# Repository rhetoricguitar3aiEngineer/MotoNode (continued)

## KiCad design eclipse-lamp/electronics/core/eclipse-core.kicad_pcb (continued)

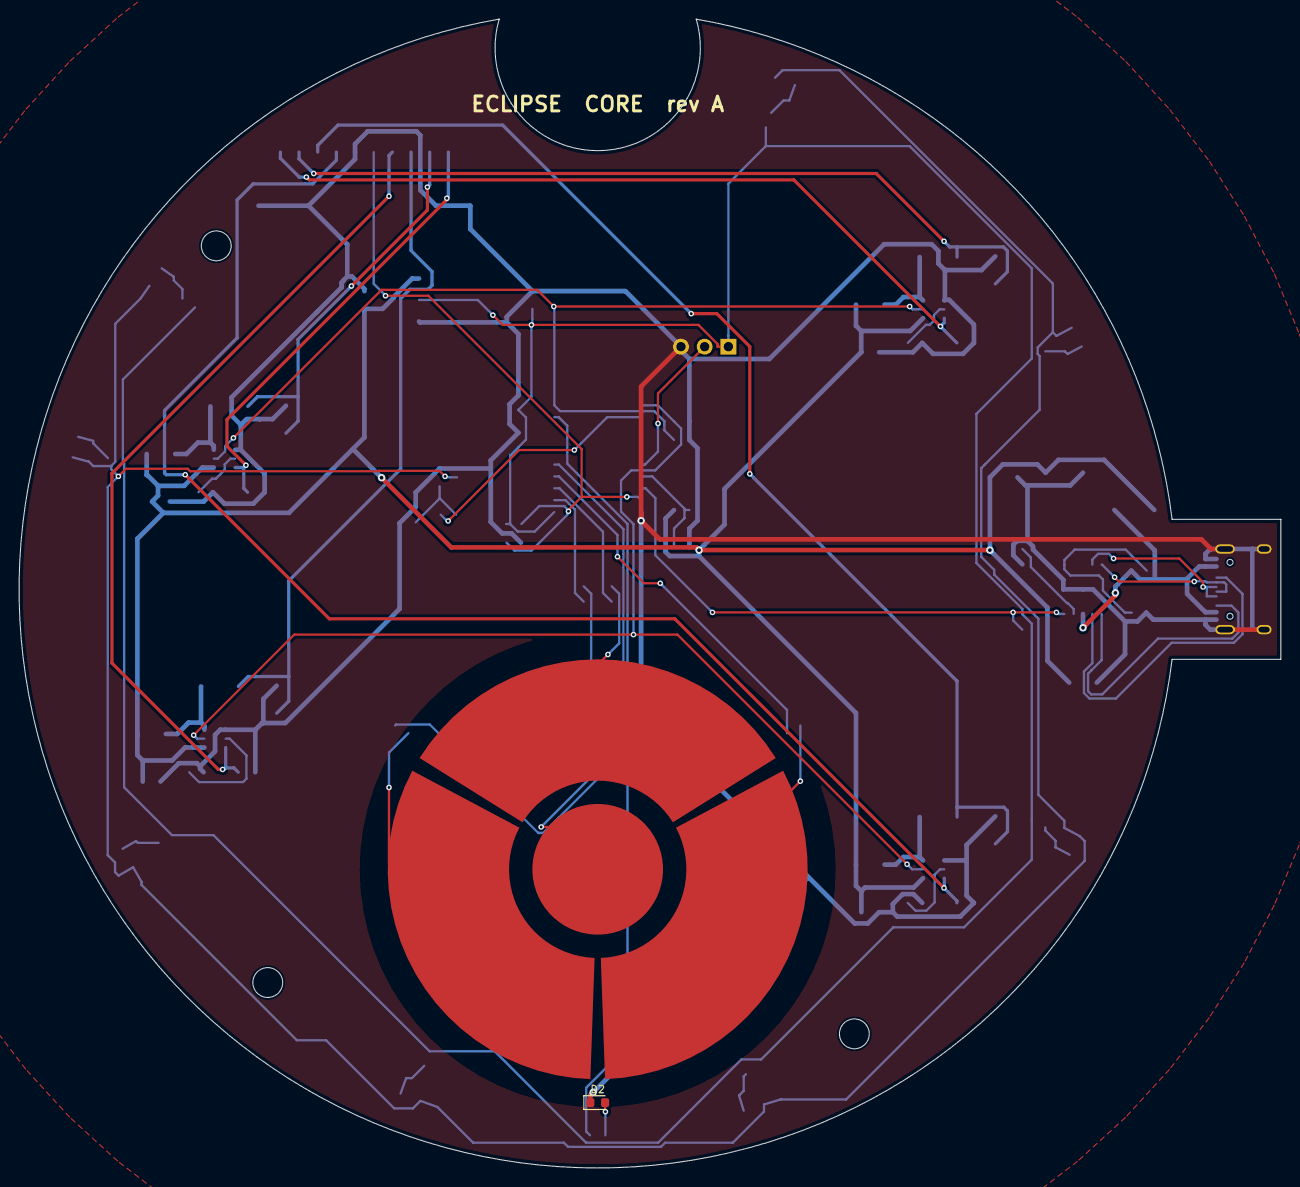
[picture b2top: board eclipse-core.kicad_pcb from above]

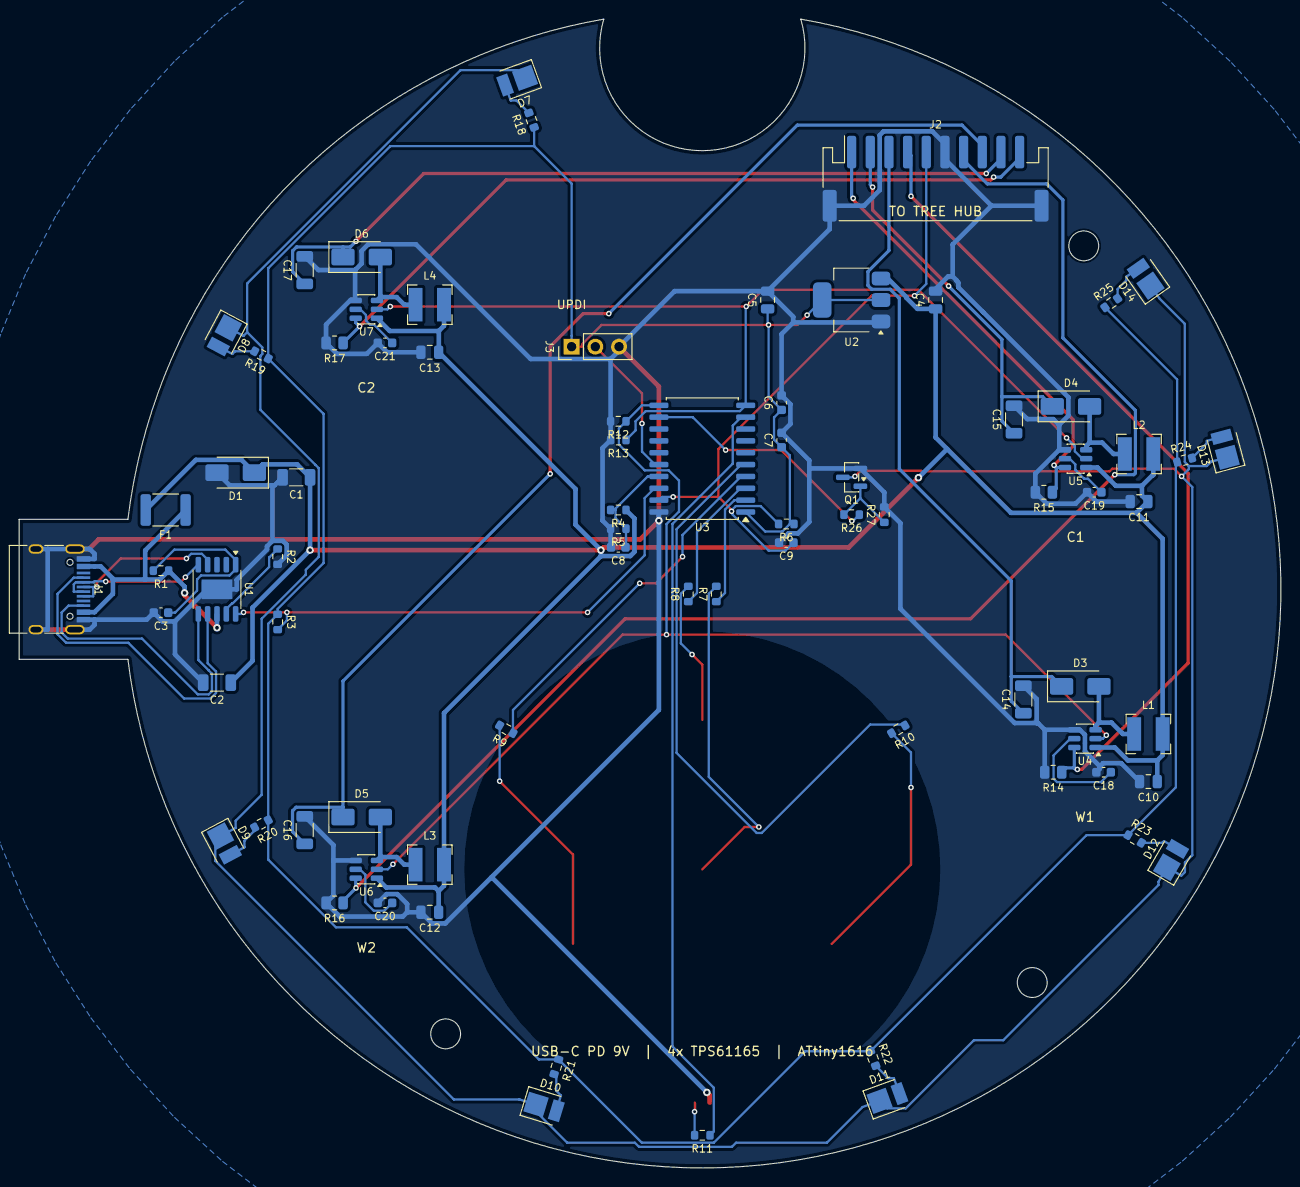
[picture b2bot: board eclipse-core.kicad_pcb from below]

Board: 2 copper layers, 135.2 x 123.1 mm, 85 parts (80 on the bottom side), 53 nets.

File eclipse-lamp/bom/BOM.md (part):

# ECLIPSE Tree - Bill of Materials

Generated by `make_bom.py` from the KiCad schematics plus the mechanical parts list.
Unit prices are **budgetary estimates** (USD, 1k-unit volume). Re-quote before ordering.

## Core board (base)

| Refs | Qty | Value | Description | Manufacturer | MPN | Unit $ | Ext $ |
|---|---:|---|---|---|---|---:|---:|
| C1,C2 | 2 | 22uF 25V | Input bulk | Murata | GRM31CR61E226KE15L | 0.060 | 0.12 |
| C3,C7 | 2 | 1uF | CH224K VDD decoupling,MCU decoupling | Murata | GRM188R61E105KA12D | 0.006 | 0.01 |
| C4 | 1 | 10uF | LDO input | Samsung | CL21A106KAYNNNE | 0.020 | 0.02 |
| C5 | 1 | 22uF | LDO output | Samsung | CL21A226MAQNNNE | 0.020 | 0.02 |
| C6,C8,C9 | 3 | 100nF | MCU decoupling | Murata | GRM188R71H104KA93D | 0.004 | 0.01 |
| C10,C11,C12,C13 | 4 | 10uF 25V | Boost input | Samsung | CL21A106KAYNNNE | 0.020 | 0.08 |
| C14,C15,C16,C17 | 4 | 1uF 50V | Boost output | Murata | GRM31MR71H105KA88L | 0.040 | 0.16 |
| C18,C19,C20,C21 | 4 | 220nF | Loop compensation | Murata | GRM188R71E224KA88D | 0.006 | 0.02 |
| D1 | 1 | SMAJ15CA | TVS 15 V standoff, bidirectional, 400 W | Littelfuse | SMAJ15CA | 0.050 | 0.05 |
| D2 | 1 | WHITE | 0603 white - glow under touch glass | Lite-On | LTW-C191TS5 | 0.030 | 0.03 |
| D3,D4,D5,D6 | 4 | MBRA160 | Schottky 60 V 1 A | onsemi | MBRA160T3G | 0.060 | 0.24 |
| D7,D8,D9,D10,D11,D12,D13,D14 | 8 | 2700K | 2835 warm white, fires down into the white-lined base cavity | Samsung | LM281B+ 2700K | 0.030 | 0.24 |
| F1 | 1 | 1.5A | PTC resettable fuse 1.5 A hold, 24 V | Bourns | MF-MSMF150/24X-2 | 0.100 | 0.10 |
| J1 | 1 | USB-C 16P | USB Type-C receptacle, 16P, SMD + THT shell | Korean Hroparts | TYPE-C-31-M-12 | 0.120 | 0.12 |
| J2 | 1 | TO HUB | PH 2.0 mm 10-pin side-entry SMD | JST | S10B-PH-SM4-TB | 0.250 | 0.25 |
| J3 | 1 | UPDI | UPDI programming header (DNP) | - | DNP (pogo pads) | 0.000 | 0.00 |
| L1,L2,L3,L4 | 4 | 10uH | 10 uH shielded, Isat 1.6 A | Bourns | SRN4018-100M | 0.120 | 0.48 |
| Q1 | 1 | AO3400A | N-MOSFET 30 V, low-side glow switch | Alpha & Omega | AO3400A | 0.030 | 0.03 |
| R1,R7,R8,R9,R10 | 5 | 1k | CH224K VDD feed,PTC series resistor | Yageo | RC0603FR-071KL | 0.002 | 0.01 |
| R2 | 1 | 6.8k | CFG1: 6.8k = 9 V request | Yageo | RC0603FR-076K8L | 0.002 | 0.00 |
| R3,R6 | 2 | 10k | NTC pull-up,PG pull-up | Yageo | RC0603FR-0710KL | 0.002 | 0.00 |
| R4,R12,R13,R27 | 4 | 100k | Gate pull-down,Keeps drivers off during reset,VIN sense divider top | Yageo | RC0603FR-07100KL | 0.002 | 0.01 |
| R5 | 1 | 15k | VIN sense divider bottom | Yageo | RC0603FR-0715KL | 0.002 | 0.00 |
| R11 | 1 | 470 | Status LED | Yageo | RC0603FR-07470RL | 0.002 | 0.00 |
| R14,R15,R16,R17 | 4 | 2.0 | Sense: 200 mV / 2.0 R = 100 mA | Yageo | RC0805FR-072RL | 0.004 | 0.02 |
| R18,R19,R20,R21,R22,R23,R24,R25,R26 | 9 | 100 | Gate series,Glow LED ballast, ~5 mA | Yageo | RC0603FR-07100RL | 0.002 | 0.02 |
| U1 | 1 | CH224K | USB PD/QC sink trigger, resistor-configured output voltage | WCH | CH224K | 0.350 | 0.35 |
| U2 | 1 | AMS1117-3.3 | LDO 3.3 V 1 A | Advanced Monolithic Systems | AMS1117-3.3 | 0.050 | 0.05 |
| U3 | 1 | ATtiny1616-S | AVR 16 kB, PTC touch, 20 MHz | Microchip | ATTINY1616-SNR | 0.850 | 0.85 |
| U4,U5,U6,U7 | 4 | TPS61165 | 38 V boost white-LED driver, 1.2 A switch | Texas Instruments | TPS61165DBVR | 0.550 | 2.20 |

**Subtotal: $5.50**

## Hub board (in the burl)

| Refs | Qty | Value | Description | Manufacturer | MPN | Unit $ | Ext $ |
|---|---:|---|---|---|---|---:|---:|
| D1,D2,D3,D4,D9,D10,D11,D12 | 8 | 2700K | Fibre-bundle light source (top), 25 mA,Trunk light-guide source (bottom), 25 mA | Samsung | LM281B+ 2700K | 0.030 | 0.24 |
| D5,D6,D7,D8,D13,D14,D15,D16 | 8 | 6500K | Fibre-bundle light source (top), 25 mA,Trunk light-guide source (bottom), 25 mA | Samsung | LM281B+ 6500K | 0.030 | 0.24 |
| TH1 | 1 | 10k B3380 | NTC 10k 1% B=3380, 0603 | Murata | NCP18XH103F03RB | 0.030 | 0.03 |

**Subtotal: $0.51**

## LED sprigs (x40 per lamp)

| Refs | Qty | Value | Description | Manufacturer | MPN | Unit $ | Ext $ |
|---|---:|---|---|---|---|---:|---:|
| D1,D2,D3,D4,D5,D6,D7,D8,D9,D10,D11,D12,D13,D14,D15,D16,D1... | 400 | LEAF 2700 K | Leaf LED 0402 white 2700 K, If 5 mA | Inolux / Lite-On (select bin) | 0402 white LED 2700 K (select bin) | 0.012 | 4.80 |
| D1,D2,D3,D4,D5,D6,D7,D8,D9,D10,D11,D12,D13,D14,D15,D16,D1... | 400 | LEAF 6500 K | Leaf LED 0402 white 6500 K, If 5 mA | Inolux / Lite-On (select bin) | 0402 white LED 6500 K (select bin) | 0.012 | 4.80 |

**Subtotal: $9.60**

## Bare PCBs

| Refs | Qty | Value | Description | Manufacturer | MPN | Unit $ | Ext $ |
|---|---:|---|---|---|---|---:|---:|
| PCB1 | 1 |  | Core PCB, D124 + USB tab, 2L 1.6 mm FR4, 1 oz, matte black, ENIG | PCB fab (e.g. JLCPCB) | eclipse-core | 1.200 | 1.20 |
| PCB2 | 1 |  | Hub light-engine PCB, D56 with D5 hole, 2L 1.0 mm FR4, white mask, ENIG, 2-side SMT | PCB fab (e.g. JLCPCB) | eclipse-hub | 0.600 | 0.60 |
| PCB3 | 40 |  | Sprig flex, 2L polyimide 0.11 mm, bronze coverlay, ENIG (panelised) | PCB fab (e.g. JLCPCB) | eclipse-sprig | 0.220 | 8.80 |

**Subtotal: $10.60**

## Mechanical

| Refs | Qty | Value | Description | Manufacturer | MPN | Unit $ | Ext $ |
|---|---:|---|---|---|---|---:|---:|
| M1 | 1 |  | Base upper shell, D150 x 12 (touch skin + trunk socket) | 6061-T6, CNC turned+milled, bead blast, graphite anodise; cavity white-painted | ECL-M-001 | 7.500 | 7.50 |
| M2 | 1 |  | Weight / reflector disc, D110 x 6.5 (~0.48 kg) | S235 steel, laser cut, white powder coat | ECL-M-002 | 1.600 | 1.60 |
| M3 | 1 |  | Root-glow band, D148/D138 x 7 | Light-diffusing PMMA, extruded tube cut + polished | ECL-M-003 | 0.700 | 0.70 |
| M4 | 1 |  | Plinth, D150 x 3 + 3 posts (~0.42 kg) | S235 steel, laser cut, posts welded, black powder coat | ECL-M-004 | 2.400 | 2.40 |
| M5 | 1 |  | Foot ring, D146/D122 x 1 | Cork/rubber composite, die cut, PSA backed | ECL-M-005 | 0.300 | 0.30 |
| M6 | 1 |  | Touch window, D52 x 3 | Soda-lime glass, satin etch top, screen-printed ring | ECL-M-006 | 1.600 | 1.60 |
| M7 | 1 |  | Trunk shell D44 -> D34, S-curved, 6 buttress roots, open bark fissures | Lost-wax cast silicon bronze, 2.5 mm wall, 2 halves | ECL-M-007 | 14.000 | 14.00 |
| M7a | 1 |  | Trunk light-guide core, 150 mm, 6 mm wire bore | Light-diffusing PMMA (LED-grade, low haze), cast + polished, white-dot extraction print | ECL-M-016 | 3.500 | 3.50 |
| M7b | 1 |  | Trunk spigot, D14 x 2 tube, 40 mm (into the base socket) | C260 brass, brazed into the trunk casting | ECL-M-017 | 0.600 | 0.60 |
| M8 | 1 |  | Burl (fork knot) D68, 2 cast halves, knot holes, houses the light engine | Lost-wax cast silicon bronze, ~180 g | ECL-M-008 | 9.000 | 9.00 |
| M9 | 1 |  | Crown: 4 limbs, 73 branches + 1222 spur twigs (5x the previous crown) | Brass tube (limbs) + C260 rod/wire D0.7-10 mm, jig-formed from the CAD skeleton, brazed | ECL-M-009 | 42.000 | 42.00 |
| M9a | 1 |  | End-glow optical fibre, 657 x 0.5 mm, ~0.3 m each, in 4 bundles | PMMA POF, end-glow, black jacket stripped at the tips | ECL-O-001 | 4.500 | 4.50 |
| M9b | 4 |  | Fibre bundle ferrule (over the hub's top LED pair) | Machined aluminium, polished fibre face, optical gel | ECL-O-002 | 0.400 | 1.60 |
| M9c | 657 |  | Samara (seed) diffuser, 6 x 4 x 1.2 mm, dip-moulded on each fibre tip | Diffusing epoxy (TiO2 0.2 %), warm tint | ECL-O-003 | 0.004 | 2.63 |
| M10 | 1 |  | Bark finish, whole tree | Brown-grey liver-of-sulphur patina + matte lacquer | ECL-M-010 | 2.500 | 2.50 |
| M11 | 1 |  | Magnet wire, 80 x 0.15 mm, ~0.35 m each, laid in branch grooves | Polyurethane-enamelled Cu (solderable), bark-colour | ECL-W-002 | 0.600 | 0.60 |
| M12 | 1 |  | Trunk harness, 10 x AWG30 PTFE, 260 mm | Hub J1 lands -> core J2 (JST PHR-10 + SPH-002T) | ECL-W-001 | 0.700 | 0.70 |
| M13 | 1 |  | Burl potting + light-engine optical gel | Black flexible epoxy (back side) + clear silicone gel (LED faces) | ECL-M-013 | 0.400 | 0.40 |
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
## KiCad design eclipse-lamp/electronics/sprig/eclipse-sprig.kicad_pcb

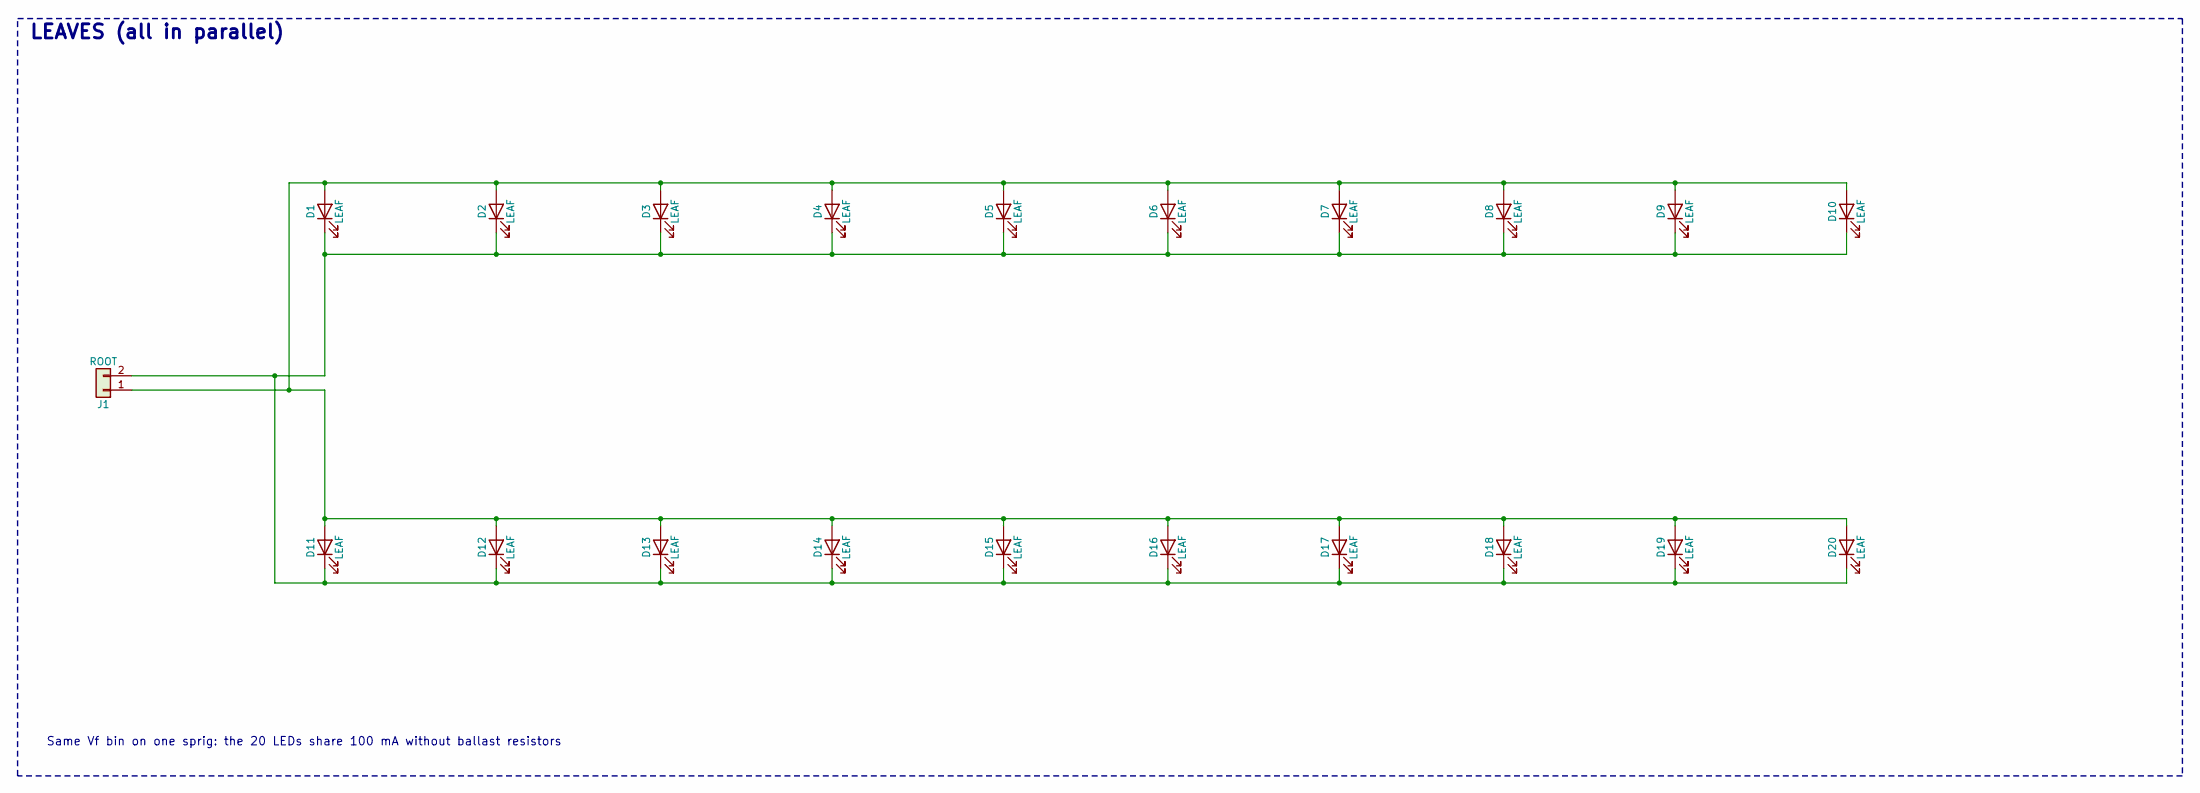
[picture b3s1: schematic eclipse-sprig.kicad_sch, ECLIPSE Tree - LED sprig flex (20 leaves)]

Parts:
D1, D2, D3, D4, D5, D6, D7, D8, D9, D10, D11, D12, D13, D14, D15, D16, D17, D18, D19, D20: LEAF; LED_0402_1005Metric; MPN 0402 white LED, 2700K or 6500K
J1: ROOT; SprigRoot; MPN PCB land

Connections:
unnamed: D1.2 (A), D2.2 (A), D3.2 (A), D4.2 (A), D5.2 (A), D6.2 (A), D7.2 (A), D8.2 (A), D9.2 (A), D10.2 (A), D11.2 (A), D12.2 (A), D13.2 (A), D14.2 (A), D15.2 (A), D16.2 (A), D17.2 (A), D18.2 (A), D19.2 (A), D20.2 (A), J1.1
unnamed: D1.1 (K), D2.1 (K), D3.1 (K), D4.1 (K), D5.1 (K), D6.1 (K), D7.1 (K), D8.1 (K), D9.1 (K), D10.1 (K), D11.1 (K), D12.1 (K), D13.1 (K), D14.1 (K), D15.1 (K), D16.1 (K), D17.1 (K), D18.1 (K), D19.1 (K), D20.1 (K), J1.2

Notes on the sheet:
LEAVES (all in parallel)
Same Vf bin on one sprig: the 20 LEDs share 100 mA without ballast resistors

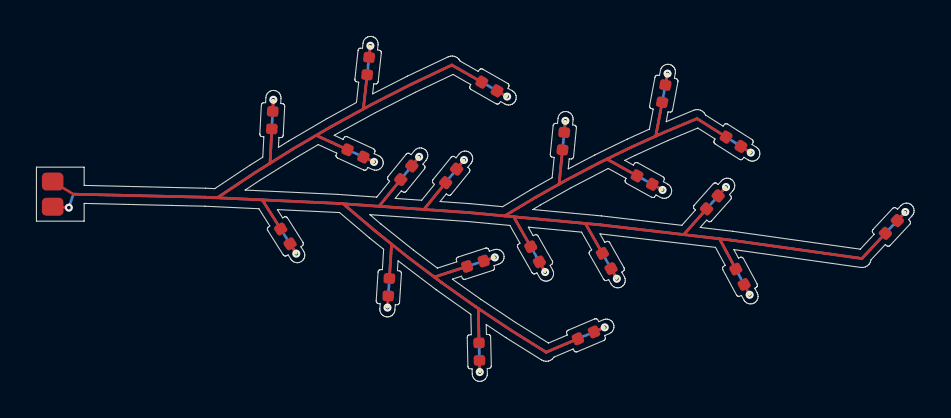
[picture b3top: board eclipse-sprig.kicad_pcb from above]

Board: 2 copper layers, 48.8 x 19.2 mm, 21 parts (0 on the bottom side), 2 nets.

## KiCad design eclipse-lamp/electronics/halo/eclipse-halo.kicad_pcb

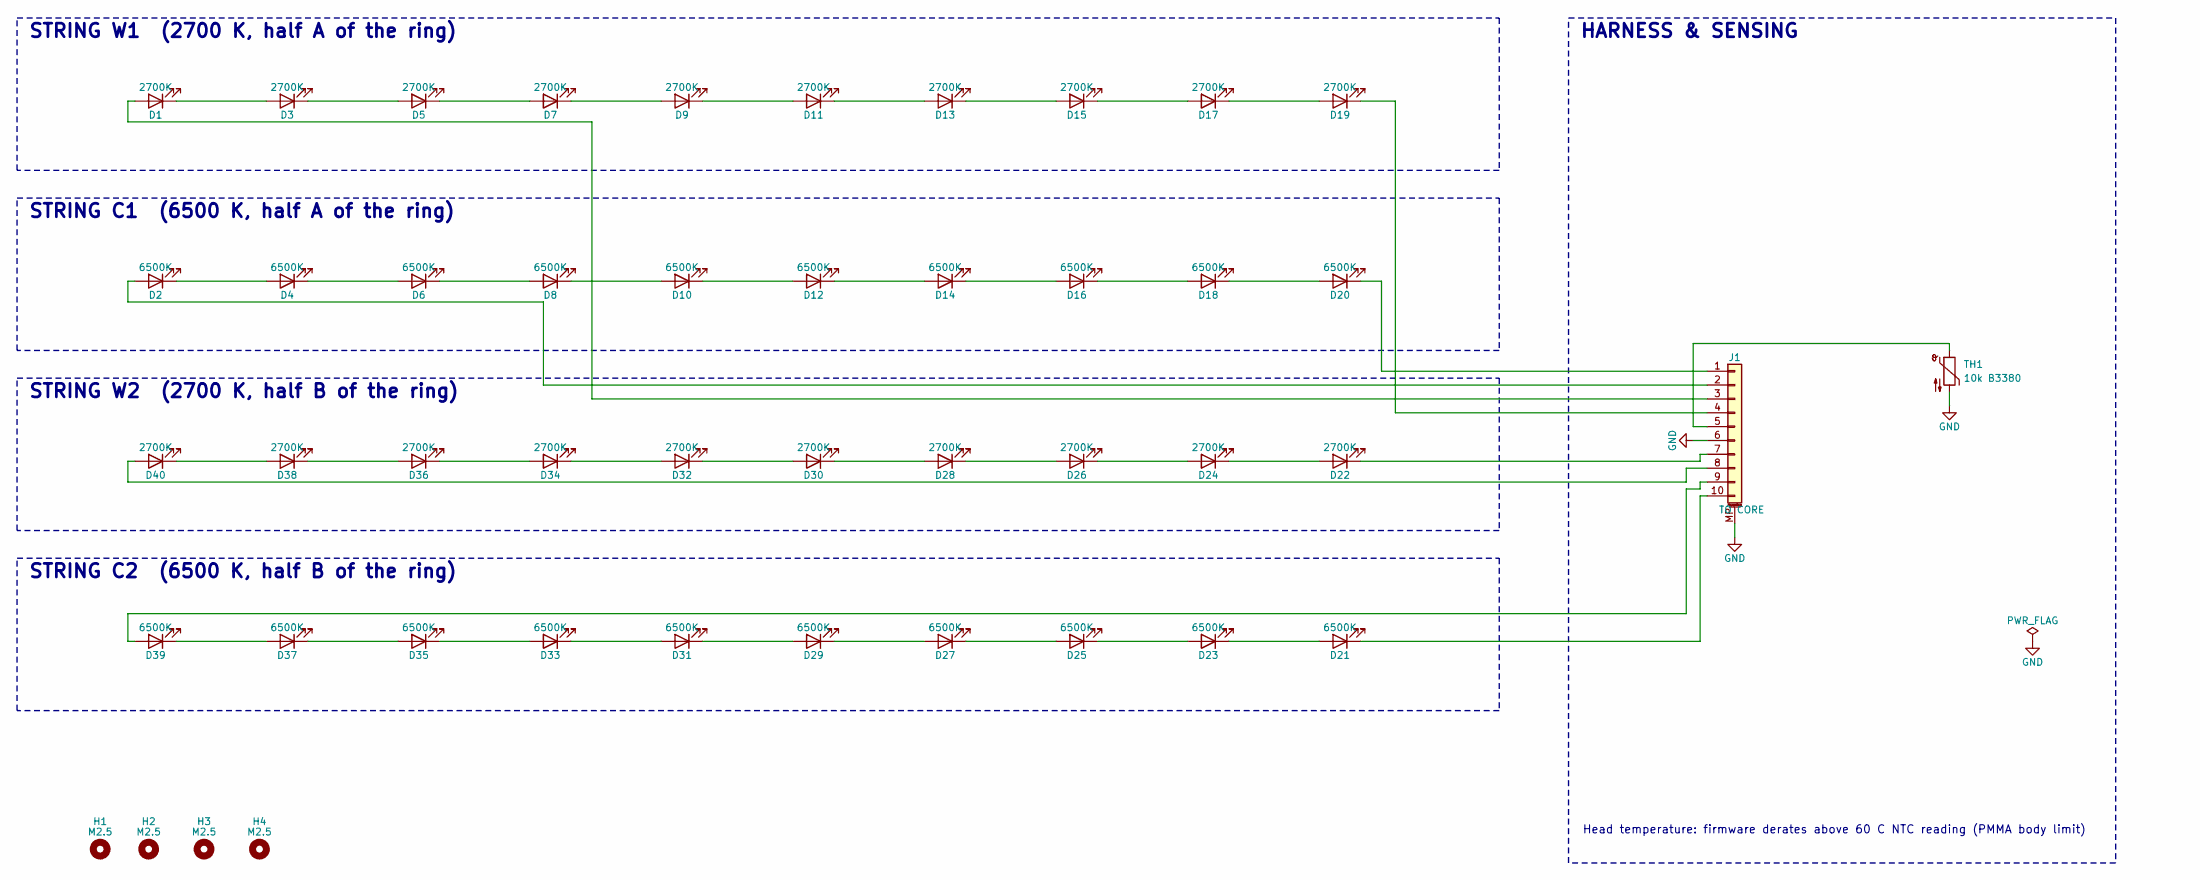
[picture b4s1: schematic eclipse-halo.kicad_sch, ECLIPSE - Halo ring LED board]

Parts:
D1, D3, D5, D7, D9, D11, D13, D15, D17, D19, D22, D24, D26, D28, D30, D32, D34, D36, D38, D40: 2700K; LED_Luminus_MP-3030-1100_3.0x3.0mm; MPN MP-3030-1100-27-90
D2, D4, D6, D8, D10, D12, D14, D16, D18, D20, D21, D23, D25, D27, D29, D31, D33, D35, D37, D39: 6500K; LED_Luminus_MP-3030-1100_3.0x3.0mm; MPN MP-3030-1100-65-90
H1, H2, H3, H4: M2.5; MountingHole_2.7mm_M2.5
J1: TO CORE; JST_PH_S10B-PH-SM4-TB_1x10-1MP_P2.00mm_Horizontal; MPN S10B-PH-SM4-TB
TH1: 10k B3380; R_0603_1608Metric; MPN NCP18XH103F03RB

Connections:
GND: J1.6, J1.MP (MountPin), TH1.2
unnamed: D1.2 (A), J1.3
unnamed: D1.1 (K), D3.2 (A)
unnamed: D2.2 (A), J1.2
unnamed: D2.1 (K), D4.2 (A)
unnamed: D3.1 (K), D5.2 (A)
unnamed: D4.1 (K), D6.2 (A)
unnamed: D5.1 (K), D7.2 (A)
unnamed: D6.1 (K), D8.2 (A)
unnamed: D7.1 (K), D9.2 (A)
unnamed: D8.1 (K), D10.2 (A)
unnamed: D10.1 (K), D12.2 (A)
unnamed: D9.1 (K), D11.2 (A)
unnamed: D11.1 (K), D13.2 (A)
unnamed: D12.1 (K), D14.2 (A)
unnamed: D13.1 (K), D15.2 (A)
unnamed: D14.1 (K), D16.2 (A)
unnamed: D15.1 (K), D17.2 (A)
unnamed: D16.1 (K), D18.2 (A)
unnamed: D17.1 (K), D19.2 (A)
unnamed: D18.1 (K), D20.2 (A)
unnamed: D19.1 (K), J1.4
unnamed: D20.1 (K), J1.1
unnamed: D21.2 (A), D23.1 (K)
unnamed: D21.1 (K), J1.10
unnamed: D22.2 (A), D24.1 (K)
unnamed: D22.1 (K), J1.7
unnamed: D23.2 (A), D25.1 (K)
unnamed: D24.2 (A), D26.1 (K)
unnamed: D25.2 (A), D27.1 (K)
unnamed: D26.2 (A), D28.1 (K)
unnamed: D27.2 (A), D29.1 (K)
unnamed: D28.2 (A), D30.1 (K)
unnamed: D29.2 (A), D31.1 (K)
unnamed: D30.2 (A), D32.1 (K)
unnamed: D31.2 (A), D33.1 (K)
unnamed: D32.2 (A), D34.1 (K)
unnamed: D33.2 (A), D35.1 (K)
unnamed: D34.2 (A), D36.1 (K)
unnamed: D35.2 (A), D37.1 (K)
unnamed: D36.2 (A), D38.1 (K)
unnamed: D37.2 (A), D39.1 (K)
unnamed: D38.2 (A), D40.1 (K)
unnamed: D39.2 (A), J1.9
unnamed: D40.2 (A), J1.8
unnamed: J1.5, TH1.1

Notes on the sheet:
STRING W1 (2700 K, half A of the ring)
STRING C1 (6500 K, half A of the ring)
STRING W2 (2700 K, half B of the ring)
STRING C2 (6500 K, half B of the ring)
HARNESS & SENSING
Head temperature: firmware derates above 60 C NTC reading (PMMA body limit)

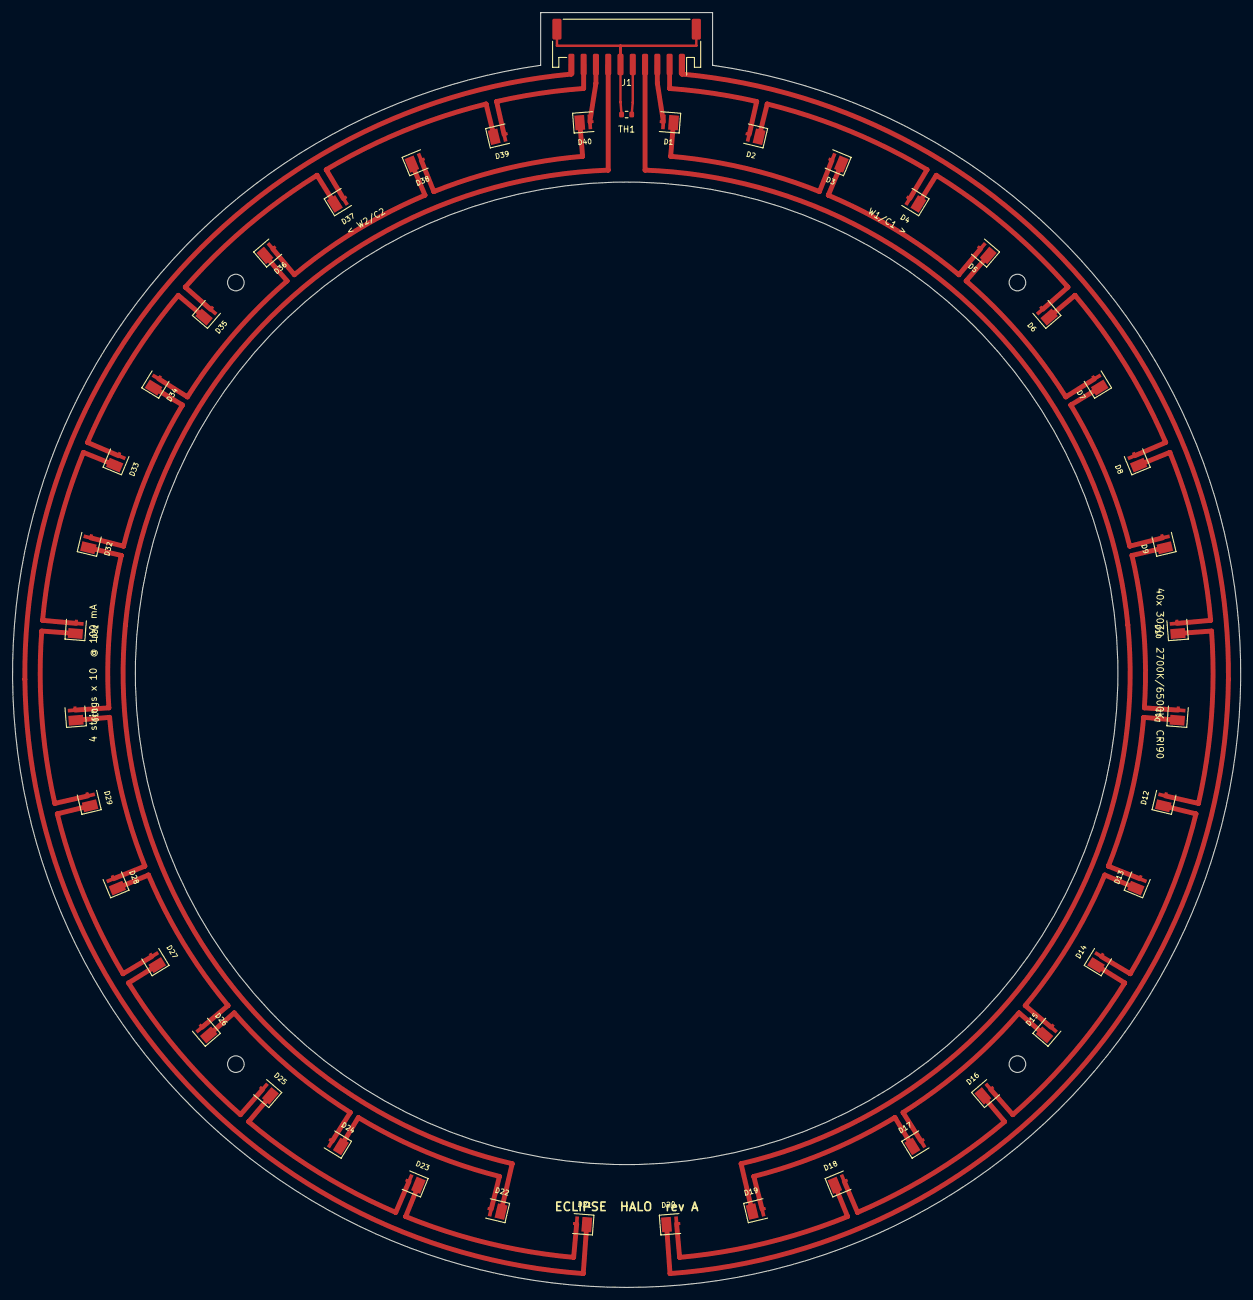
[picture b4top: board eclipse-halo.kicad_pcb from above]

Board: 2 copper layers, 200.0 x 207.6 mm, 46 parts (0 on the bottom side), 46 nets.
